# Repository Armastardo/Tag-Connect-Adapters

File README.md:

# Tag-Connect-Adapters
Made for the 6 pin 0.1" TC2030-IDC-NL

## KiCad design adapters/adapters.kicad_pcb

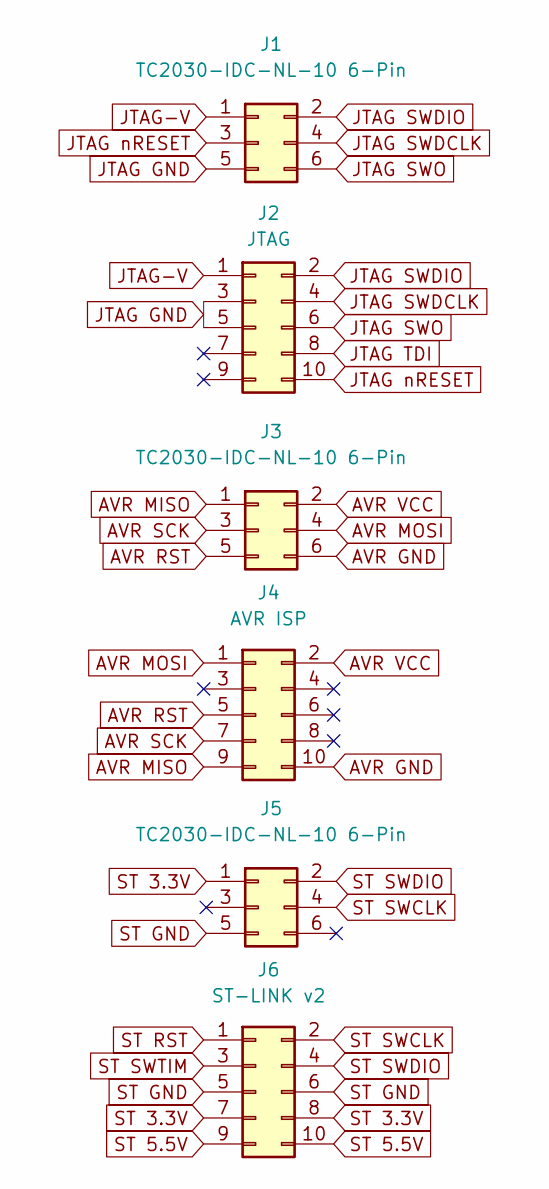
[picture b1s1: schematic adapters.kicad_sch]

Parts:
J1, J3, J5: TC2030-IDC-NL-10 6-Pin; PinHeader_2x03_P2.54mm_Vertical
J2: JTAG; PinHeader_2x05_P1.27mm_Vertical_SMD
J4: AVR ISP; PinHeader_2x05_P2.54mm_Vertical
J6: ST-LINK v2; PinHeader_2x05_P2.54mm_Vertical

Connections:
AVR GND: J3.6, J4.10
AVR MISO: J3.1, J4.9
AVR MOSI: J3.4, J4.1
AVR RST: J3.5, J4.5
AVR SCK: J3.3, J4.7
AVR VCC: J3.2, J4.2
JTAG GND: J1.5, J2.3, J2.5
JTAG SWDCLK: J1.4, J2.4
JTAG SWDIO: J1.2, J2.2
JTAG SWO: J1.6, J2.6
JTAG TDI: J2.8
JTAG nRESET: J1.3, J2.10
JTAG-V: J1.1, J2.1
ST 3.3V: J5.1, J6.7, J6.8
ST 5.5V: J6.9, J6.10
ST GND: J5.5, J6.5, J6.6
ST RST: J6.1
ST SWCLK: J5.4, J6.2
ST SWDIO: J5.2, J6.4
ST SWTIM: J6.3

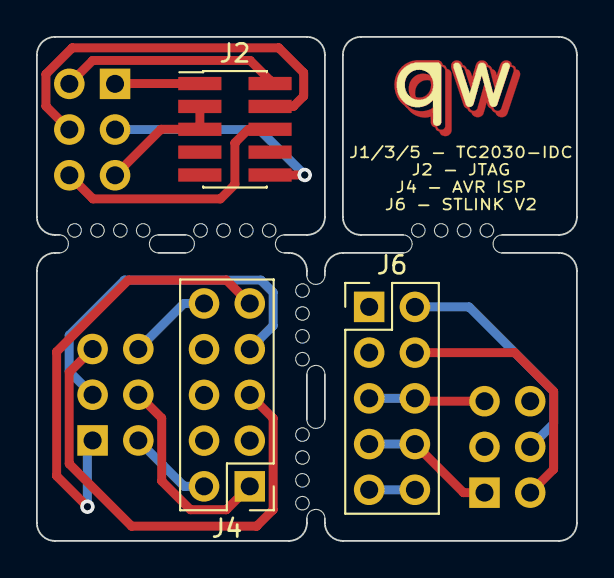
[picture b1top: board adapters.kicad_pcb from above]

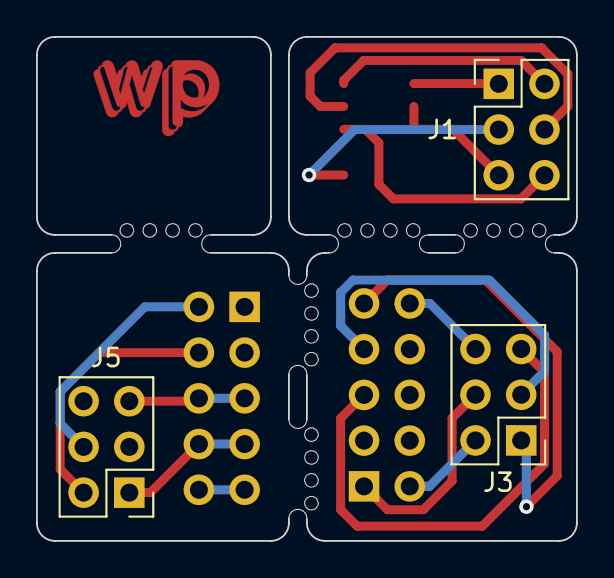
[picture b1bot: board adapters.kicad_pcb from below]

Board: 2 copper layers, 30.0 x 28.0 mm, 7 parts (3 on the bottom side), 17 nets.

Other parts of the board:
Ref**: Val**; qw-logo-small

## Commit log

2022-04-27 First revision of the PCB
